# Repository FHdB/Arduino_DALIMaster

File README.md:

# Arduino DALI Master
Simple Arduino Shield to work with LEDWARRIOR09MOD. It can send DALI dim values to DALI ballasts. Works with 7segment rotary encoder project: https://github.com/FHdB/7Segment-Display-with-Rotary-Encoder

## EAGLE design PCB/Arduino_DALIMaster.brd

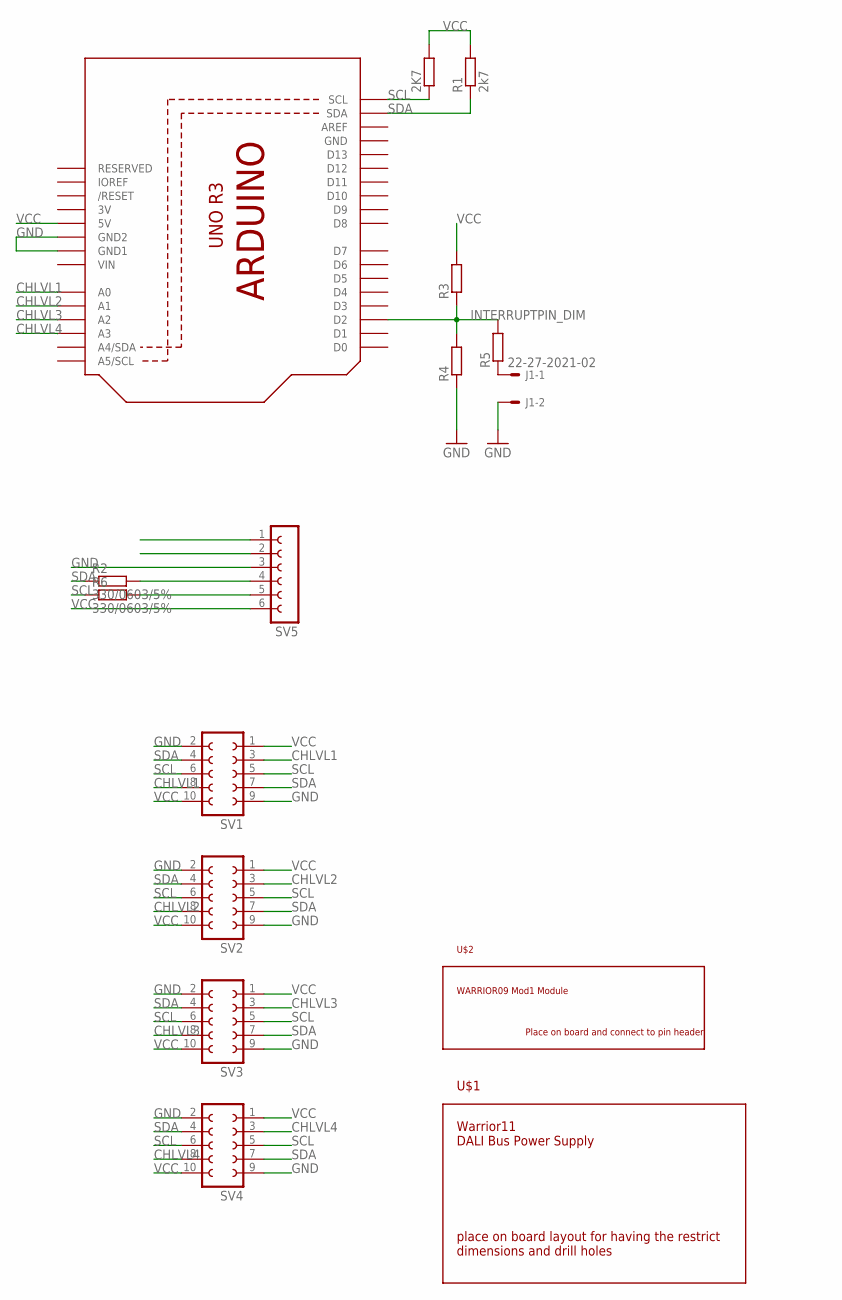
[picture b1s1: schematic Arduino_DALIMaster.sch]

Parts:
2K7: R-EU_R0603; R0603
J1: 22-27-2021-02; 6410-02
R1: 2k7; R0603
R2, R6: 330/0603/5%; R0603
R3, R4, R5: R-EU_R0603; R0603
SV1, SV2, SV3, SV4: FE05-2
SV5: FE06-1; FE06
U1: ARDUINOR3-BPLACE
U$1: WARRIOR11
U$2: WARRIOR09MOD1; WARRIOR09

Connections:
3V: U1.3V
CHLVL1: SV1.3, SV1.8, U1.A0
CHLVL2: SV2.3, SV2.8, U1.A1
CHLVL3: SV3.3, SV3.8, U1.A2
CHLVL4: SV4.3, SV4.8, U1.A3
GND: J1.2, R4.1, SV1.2, SV1.9, SV2.2, SV2.9, SV3.2, SV3.9, SV4.2, SV4.9, SV5.3, U1.GND, U1.GND1, U1.GND2
INTERRUPTPIN_DIM: R3.1, R4.2, R5.2, U1.D2
unnamed: J1.1, R5.1
unnamed: R2.2, SV5.4
unnamed: R6.2, SV5.5
SCL: 2K7.1, R6.1, SV1.5, SV1.6, SV2.5, SV2.6, SV3.5, SV3.6, SV4.5, SV4.6, U1.SCL
SDA: R1.1, R2.1, SV1.4, SV1.7, SV2.4, SV2.7, SV3.4, SV3.7, SV4.4, SV4.7, U1.SDA
VCC: 2K7.2, R1.2, R3.2, SV1.1, SV1.10, SV2.1, SV2.10, SV3.1, SV3.10, SV4.1, SV4.10, SV5.6, U1.5V
VIN: U1.VIN

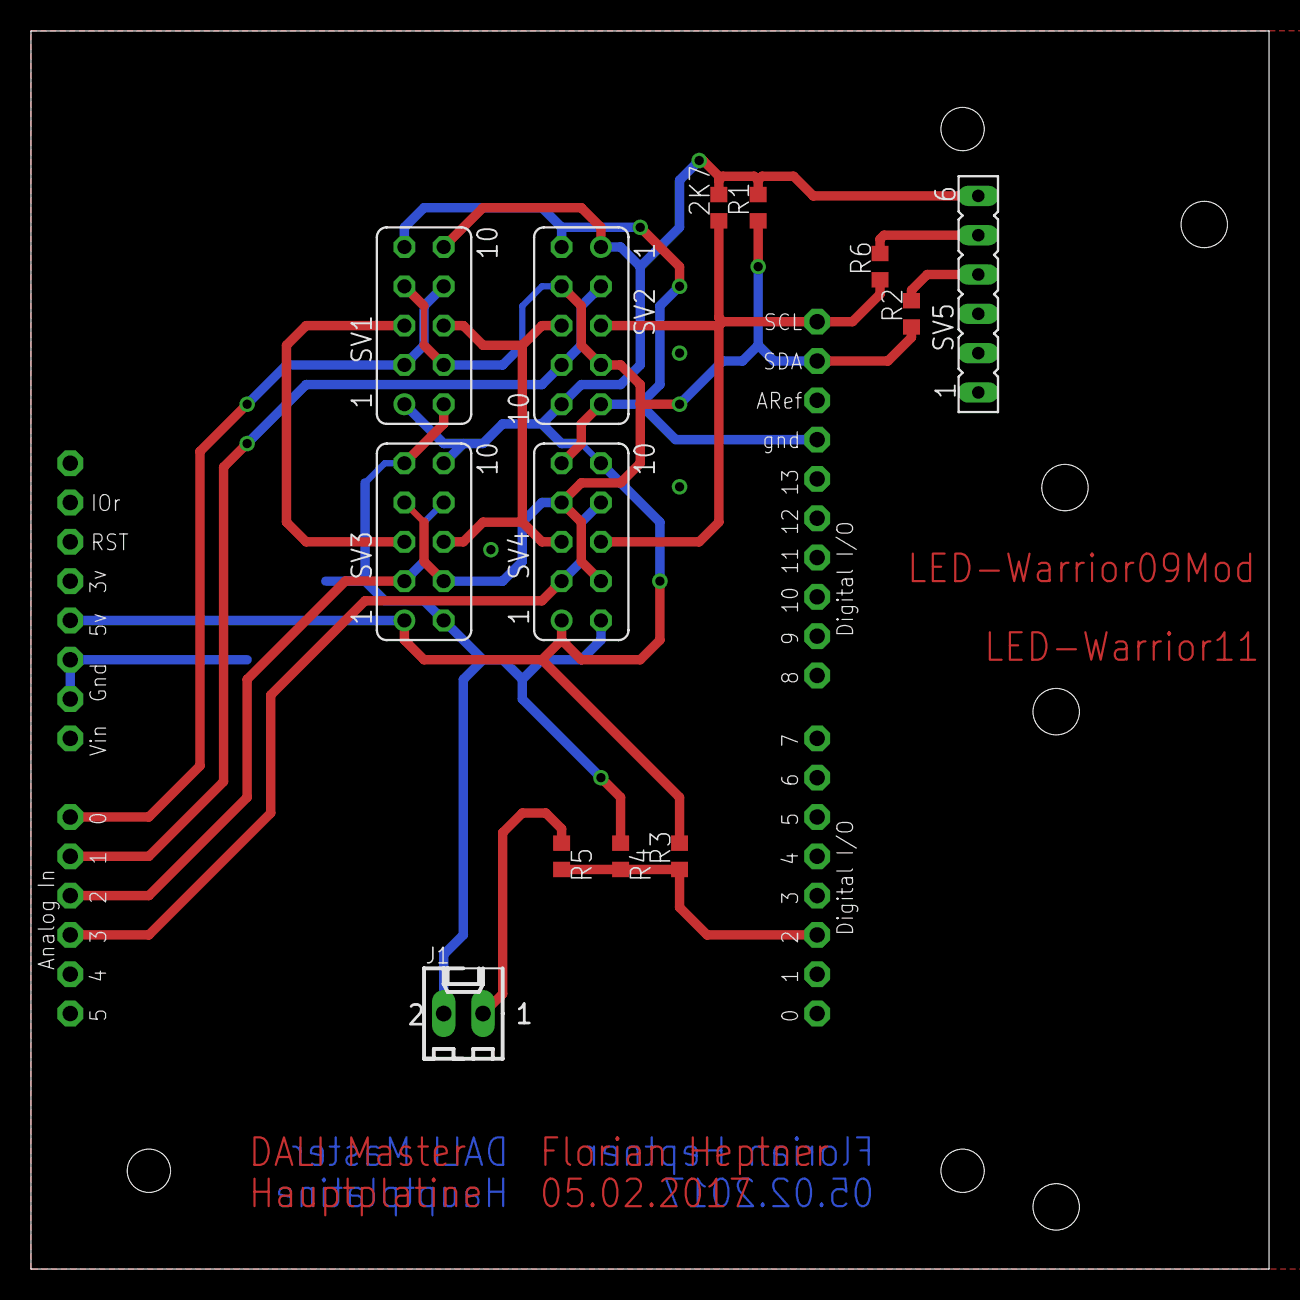
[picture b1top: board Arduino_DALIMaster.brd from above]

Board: 2 copper layers, 80.0 x 80.0 mm, 16 parts (0 on the bottom side), 12 nets.

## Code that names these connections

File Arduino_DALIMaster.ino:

// DALI Master Arduino Code
// by Florian Heptner https://github.com/FHdB

/*
This program is free software: you can redistribute it and/or modify
it under the terms of the GNU General Public License as published by
the Free Software Foundation, either version 3 of the License, or
(at your option) any later version.
This program is distributed in the hope that it will be useful,
but WITHOUT ANY WARRANTY; without even the implied warranty of
MERCHANTABILITY or FITNESS FOR A PARTICULAR PURPOSE.  See the
GNU General Public License for more details.
You should have received a copy of the GNU General Public License
along with this program.  If not, see <http://www.gnu.org/licenses/>.
Dieses Programm ist Freie Software: Sie können es unter den Bedingungen
der GNU General Public License, wie von der Free Software Foundation,
Version 3 der Lizenz oder (nach Ihrer Wahl) jeder neueren
veröffentlichten Version, weiterverbreiten und/oder modifizieren.
Dieses Programm wird in der Hoffnung, dass es nützlich sein wird, aber
OHNE JEDE GEWÄHRLEISTUNG, bereitgestellt; sogar ohne die implizite
Gewährleistung der MARKTFÄHIGKEIT oder EIGNUNG FÜR EINEN BESTIMMTEN ZWECK.
Siehe die GNU General Public License für weitere Details.
Sie sollten eine Kopie der GNU General Public License zusammen mit diesem
Programm erhalten haben. Wenn nicht, siehe <http://www.gnu.org/licenses/>.
*/
/*
DALI Master Arduino Code
Made for being used in combination with seven segment and rotary encoder module
https://github.com/FHdB/7Segment-Display-with-Rotary-Encoder/blob/master/SevSegment_RotaryEncoder/SevSegment_RotaryEncoder.ino
*/

#include <Wire.h>

#define  CHLVL1 A0
#define  CHLVL2 A1
#define  CHLVL3 A2
#define  CHLVL4 A3

uint8_t i2c_rec[6];
uint8_t dimValue[] = {0 , 0 , 0 ,0 };
uint8_t address[]  = {233 , 233 , 233 ,233 };

// Warrior defines
#define warrior_addr 0b100000

// dim button
#define INTERRUPTPIN_DIM 2
boolean button_pressed = false;

void setup()
{
  Wire.begin();        // join i2c bus (address optional for master)
  Wire.setClock(50000L);
  Serial.begin(9600);  // start serial for output
  Serial.println("Start");
  pinMode(2,INPUT);
  
  //change level pins
  pinMode(CHLVL1, INPUT);
  digitalWrite(CHLVL1 ,LOW);
  pinMode(CHLVL2, INPUT);
  digitalWrite(CHLVL2 ,LOW);
  pinMode(CHLVL3, INPUT);
  digitalWrite(CHLVL3 ,LOW);
  pinMode(CHLVL4, INPUT);
  digitalWrite(CHLVL4 ,LOW);
  
  //interrupt pin
  pinMode(INTERRUPTPIN_DIM, INPUT);
  pciSetup(INTERRUPTPIN_DIM);
}

void loop()
{
  int pin_1_state = digitalRead(A0);
  int pin_2_state = digitalRead(A1);
  int pin_3_state = digitalRead(A2);
  int pin_4_state = digitalRead(A3);
  if(pin_1_state==1u)
  {
    Serial.println("requesting");
    requestDimAndAddr(2u, 0u);
    Serial.println("finished");
  }
  
//  if(pin_2_state==1u)
//  {
//    Serial.println("requesting");
//    requestDimAndAddr(3u, 1);
//    Serial.println("finished");
//  }
//  if(pin_3_state==1u)
//  {
//    Serial.println("requesting");
//    requestDimAndAddr(4u, 2);
//    Serial.println("finished");
//  }
//  if(pin_4_state==1u)
//  {
//    Serial.println("requesting");
//    requestDimAndAddr(5u, 3);
//    Serial.println("finished");
//  }
    
  if(button_pressed)
  {
    dali_dim_dev(address[0], dimValue[0]);
//    dali_dim_dev(address[1], dimValue[1]);
//    dali_dim_dev(address[2], dimValue[2]);
//    dali_dim_dev(address[3], dimValue[3]);
    button_pressed = false;
    //pciSetup(INTERRUPTPIN_DIM);
  }
}

void requestDimAndAddr(uint8_t i2c_addr, uint8_t index)
  {
    Wire.requestFrom(i2c_addr, 6);    // request 6 bytes from slave device #2
  
    uint8_t i = 0;
    while (Wire.available())   // slave may send less than requested
    {
      uint8_t c = Wire.read(); // receive a byte as character
      i2c_rec[i] = 0;
      i2c_rec[i] = c;
      i++;
    }
    
    if(i2c_rec[0] == 'a')
    {
      address[index]  = i2c_rec[1];
    }
  
    if(i2c_rec[3] == 'd')
    {
      dimValue[index] = i2c_rec[4];
    }
    Serial.print("address: ");
    Serial.println(address[index],DEC);
    Serial.print("dimValue: ");
    Serial.println(dimValue[index],DEC);
  }
  
void setDimAndAddr(uint8_t i2c_addr, uint8_t index)
{
  uint8_t sendArray[] = {'a',0,' ','d',0,' '};
  Serial.println("Sending: ");
  sendArray[1] = (address[index]+1)&(0xFF);
  Serial.print("address: ");
  Serial.println(sendArray[1]);
  sendArray[4] = (dimValue[index]+1)&(0xFF);
  Serial.print("dimValue: ");
  Serial.println(sendArray[4]);

  Serial.println("-------");

  Wire.beginTransmission(2); // transmit to device #8
  Wire.write(sendArray,6);        // sends five bytes
  boolean ok = Wire.endTransmission();    // stop transmitting

  if(ok!=0)
  {
    Serial.print("Transmission success: ");
    Serial.println(ok);
  }
}


/*------------------------------*/

// DALI Adapter Warrior09 commands

boolean dali_dim_dev(uint8_t dali_addr, uint8_t dali_dim){
  //dali_addr is expected to be a value from 0 to 64
  //if dali_addr = 0 : broadcast
  if(dali_addr==0u)
  {
    dali_addr = 0b01111111;
  }else{
    //make sure that dali_addr is max 63
    dali_addr = dali_addr&0b00111111;
    dali_addr = dali_addr-1;
  }
  
  //dali_dim is expected to be a value from 0 to 100
  // map to 0:254
  dali_dim = map(dali_dim,0,100,0,254);  
  
    uint8_t dali_bus_status = 1;
    
    Wire.requestFrom(warrior_addr,1);
    while(Wire.available()){
      dali_bus_status = Wire.read();
      Serial.println(dali_bus_status,BIN);
      if(dali_bus_status)
         {
           Serial.println("DALI BUS not ready");   
         }
    }

    //if DALI BUS is ready (==0) send dim command to addr       
    if(!dali_bus_status){
        Serial.print("Writing DALI Addr: ");
        Serial.println(dali_addr);
        
        Wire.beginTransmission(warrior_addr); // transmit to device #4
        Wire.write(0x01);
        Wire.write((dali_addr<<1));
        Wire.write(dali_dim);
        boolean bus_ack = Wire.endTransmission();    // stop transmitting
        if(bus_ack==0){
            Serial.print("Command: ");
            Serial.println((dali_addr<<1),BIN);
            Serial.println("Succesfully sent");         
        }
    }
}



/*Inhterrupt Section*/
// enable interrupt for pin
void pciSetup(byte pin)
{
    *digitalPinToPCMSK(pin) |= bit (digitalPinToPCMSKbit(pin));  // enable pin
    PCIFR  |= bit (digitalPinToPCICRbit(pin)); // clear any outstanding interrupt
    PCICR  |= bit (digitalPinToPCICRbit(pin)); // enable interrupt for the group
}

//disable interrupt
void pciTurnOff(byte pin)
{
    *digitalPinToPCMSK(pin) = *digitalPinToPCMSK(pin) &~ (bit (digitalPinToPCMSKbit(pin)));  // disable pin
    PCIFR  |= bit (digitalPinToPCICRbit(pin)); // clear any outstanding interrupt
    PCICR  |= bit (digitalPinToPCICRbit(pin)); // enable interrupt for the group
}



// Interrupt service routine for "dim" button
ISR (PCINT2_vect) // handle pin change interrupt for 1 to 7 (I think...) here
{
  Serial.println("Pin 2 interrupt");
  //pciTurnOff(INTERRUPTPIN_DIM);
  button_pressed = true;
}

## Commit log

2016-12-05 :octocat: Added .gitattributes & .gitignore files
2016-12-05 inital commit of DALIMaster PCB
    untested, unreviewed
2017-01-29 DRC
    DRC and fixing
2017-02-04 SMT parts and rerouting
    replaced all wired passives with 0603 SMT packages, rewired some of the
    connections, reduced board size to 80x90mm
2017-02-04 updated licence files
2017-02-05 Inscriptions
    Name and positions of modules
2017-02-23 Arduino Code
    Arduino Uno code for DALI Master PCB. Works with LED-Warrior09Mod. Made
    for combining with Seven Segment rotary encoder project.
